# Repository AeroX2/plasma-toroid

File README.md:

# Plasma Toroid

This project is a modification of the amazing project that is currently being hosted here
https://hackaday.io/project/194683-plasma-toroid-sky-guided-pcb-edition

# Notable Changes
- Added USB-PD built in
- Removed the arc lighter, since the parts are hard to find and expensive
  - Will probably revisit this in the future
- Trying out two MOSFETs to see heat dissipation, will update the design once I've determined a winner

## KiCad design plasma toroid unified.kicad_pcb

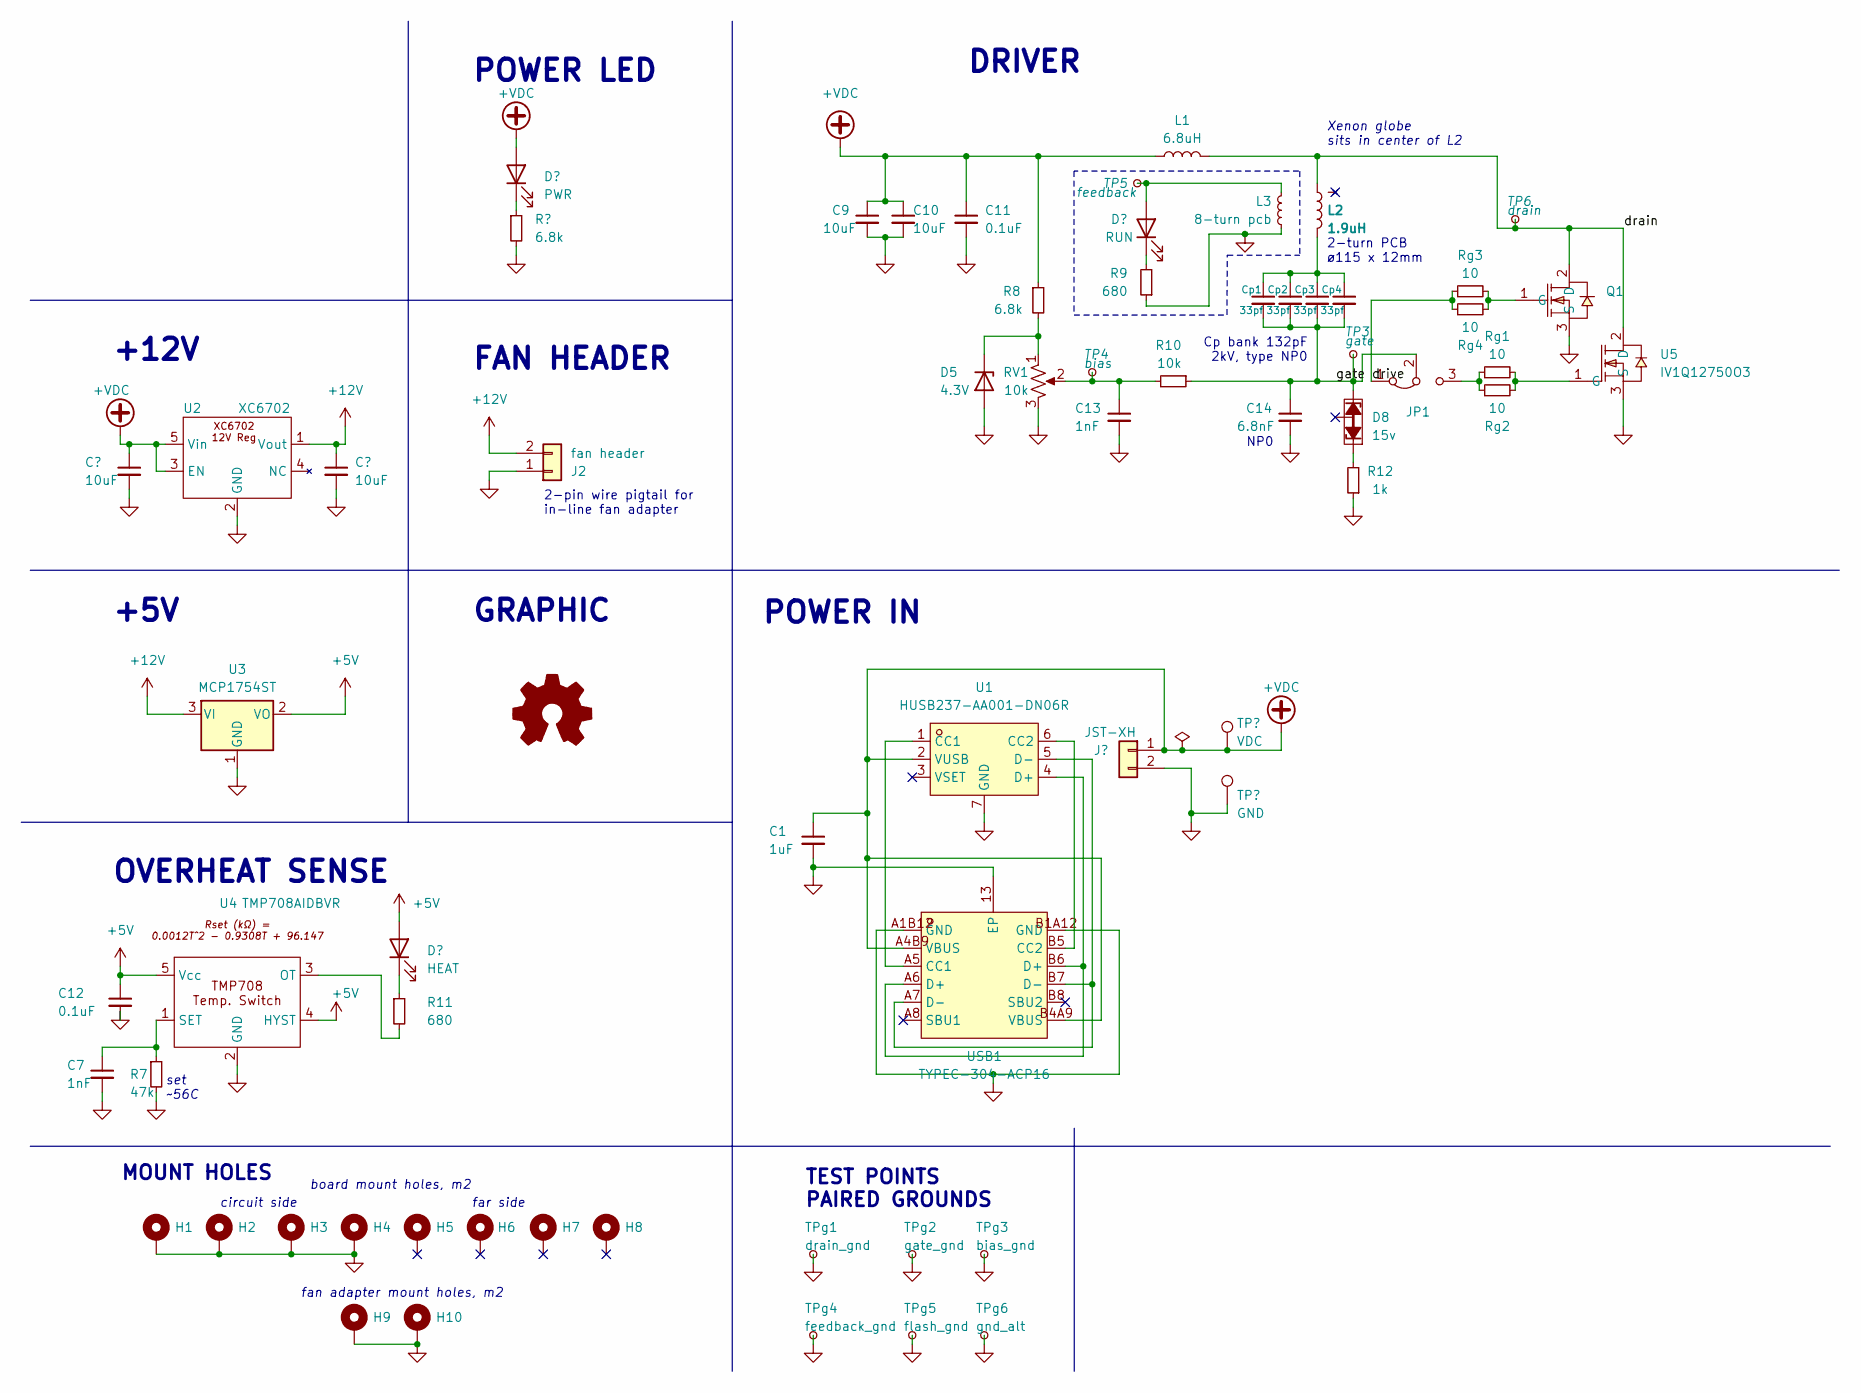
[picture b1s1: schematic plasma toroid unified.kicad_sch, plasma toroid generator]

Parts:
C1: 1uF; C_0603_1608Metric
C4, C5, C9, C10: 10uF; C_1206_3216Metric
C7, C13: 1nF; C_0603_1608Metric
C11, C12: 0.1uF; C_0603_1608Metric
C14: 6.8nF; C_1206_3216Metric
Cp1, Cp2, Cp3, Cp4: 33pf; C_1808_HandSolder
D3: PWR; LED_1206_3216Metric
D5: 4.3V; D_SOD-123
D6: RUN; LED_1206_3216Metric
D7: HEAT; LED_1206_3216Metric
D8: 15v; TSOT-23
H1, H2, H3, H4, H5, H6, H7, H8, H9, H10: MountingHole; MountingHole_2.2mm_M2_Pad_Via_3.75mmHead
J1: JST-XH; JST_PH_B2B-PH-K_1x02_P2.00mm_Vertical
J2: fan header; PinSocket_1x02_P2.00mm_Vertical
JP1: Jumper_3_Bridged12; SolderJumper-3_P1.3mm_Bridged2Bar12_RoundedPad1.0x1.5mm_Num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
L1: 6.8uH; L_Bourns_SRR1260_nosilkscreen
L2: 1.9uH; plasmadonut_inductor_2layer_115mm_integrated
L3: 8-turn pcb; FEEDBACK_COIL
Q1: NCEP02525F; TO-220F-3_L10.2-W4.7-P2.54-L; LCSC Part C503036
R4: 6.8k; R_0603_1608Metric
R7: 47k; R_0603_1608Metric
R8: 6.8k; R_1206_3216Metric
R9, R11: 680; R_0603_1608Metric
R10: 10k; R_1206_3216Metric
R12: 1k; R_1206_3216Metric
RV1: 10k; Potentiometer_Bourns_PTV09A-1_Single_Vertical_larger_mount_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
Rg1, Rg2, Rg3, Rg4: 10; R_2010_5025Metric
SYM1: Logo_Open_Hardware_Small; OSHW-Symbol_6.7x6mm_Copper
TP1: GND; TestPoint_THTPad_D2.0mm_Drill1.0mm
TP2: VDC; TestPoint_THTPad_D2.0mm_Drill1.0mm
TP3: gate; TestPoint_THTPad_D2.0mm_Drill1.0mm
TP4: bias; TestPoint_THTPad_D2.0mm_Drill1.0mm
TP5: feedback; TestPoint_THTPad_D2.0mm_Drill1.0mm
TP6: drain; TestPoint_THTPad_D2.0mm_Drill1.0mm
TPg1: drain_gnd; TestPoint_THTPad_1.0x1.0mm_Drill0.5mm
TPg2: gate_gnd; TestPoint_THTPad_1.0x1.0mm_Drill0.5mm
TPg3: bias_gnd; TestPoint_THTPad_1.0x1.0mm_Drill0.5mm
TPg4: feedback_gnd; TestPoint_THTPad_1.0x1.0mm_Drill0.5mm
TPg5: flash_gnd; TestPoint_THTPad_1.0x1.0mm_Drill0.5mm
TPg6: gnd_alt; TestPoint_THTPad_D2.5mm_Drill1.2mm
U1: HUSB237-AA001-DN06R; TDFN-6_L2.0-W2.0-P0.65-TL-EP; LCSC Part C22373734
U2: XC6702; SOT-89-5
U3: MCP1754ST; SOT-23
U4: TMP708AIDBVR; SOT-23-5
U5: IV1Q12750O3; TO-220-3_L10.2-W4.5-P2.54-L; LCSC Part C2979250
USB1: TYPEC-304-ACP16; USB-C-SMD_TYPE-C-16P-1; LCSC Part C2982555

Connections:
+5V: C12.1, D7.2 (A), U3.2 (VO), U4.4 (HYST), U4.5 (Vcc)
+12V: C5.1, J2.2, U2.1 (Vout), U3.3 (VI)
+VDC: C1.1, C4.1, C9.1, C10.1, C11.1, D3.2 (A), J1.1, L1.1, R8.1, TP2.1, U1.2 (VUSB), U2.3 (EN), U2.5 (Vin), USB1.A4B9 (VBUS), USB1.B4A9 (VBUS)
/drain: L1.2, L2.2, Q1.2 (D), TP6.1, U5.2 (D)
/gate drive: C14.1, Cp1.2, Cp2.2, Cp3.2, Cp4.2, D8.2 (A), JP1.2 (C), R10.1, TP3.1
GND: C1.2, C4.2, C5.2, C7.2, C9.2, C10.2, C11.2, C12.2, C13.2, C14.2, D5.2 (A), H1.1, H2.1, H3.1, H4.1, H9.1, H10.1, J1.2, J2.1, L3.1, Q1.3 (S), R4.2, R7.2, R9.1, R12.1, RV1.3, TP1.1, TPg1.1, TPg2.1, TPg3.1, TPg4.1, TPg5.1, TPg6.1, U1.7 (GND), U2.2 (GND), U3.1 (GND), U4.2 (GND), U5.3 (S), USB1.13 (EP), USB1.A1B12 (GND), USB1.B1A12 (GND)
unnamed: C13.1, R10.2, RV1.2, TP4.1
unnamed: Cp1.1, Cp2.1, Cp3.1, Cp4.1, L2.1
unnamed: D3.1 (K), R4.1
unnamed: D5.1 (K), R8.2, RV1.1
unnamed: D6.2 (A), L3.2, TP5.1
unnamed: D6.1 (K), R9.2
unnamed: D7.1 (K), R11.1
unnamed: D8.1 (K), R12.2
unnamed: JP1.1 (A), Rg3.1, Rg4.1
unnamed: JP1.3 (B), Rg1.1, Rg2.1
unnamed: Q1.1 (G), Rg3.2, Rg4.2
unnamed: U1.1 (CC1), USB1.A5 (CC1)
unnamed: U1.6 (CC2), USB1.B5 (CC2)
unnamed: U1.4 (D+), USB1.A6 (D+), USB1.B6 (D+)
unnamed: U1.5 (D-), USB1.A7 (D-), USB1.B7 (D-)
unnamed: R11.2, U4.3 (OT)
unnamed: C7.1, R7.1, U4.1 (SET)
unnamed: Rg1.2, Rg2.2, U5.1 (G)

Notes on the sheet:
Xenon globe sits in center of L2
POWER IN
TEST POINTS PAIRED GROUNDS
GRAPHIC
board mount holes, m2
DRIVER
FAN HEADER
POWER LED
fan adapter mount holes, m2
NP0
+12V
2-pin wire pigtail for in-line fan adapter
2-turn PCB ø115 x 12mm
MOUNT HOLES
+5V
circuit side
far side
Cp bank 132pF 2kV, type NP0
set ~56C
OVERHEAT SENSE

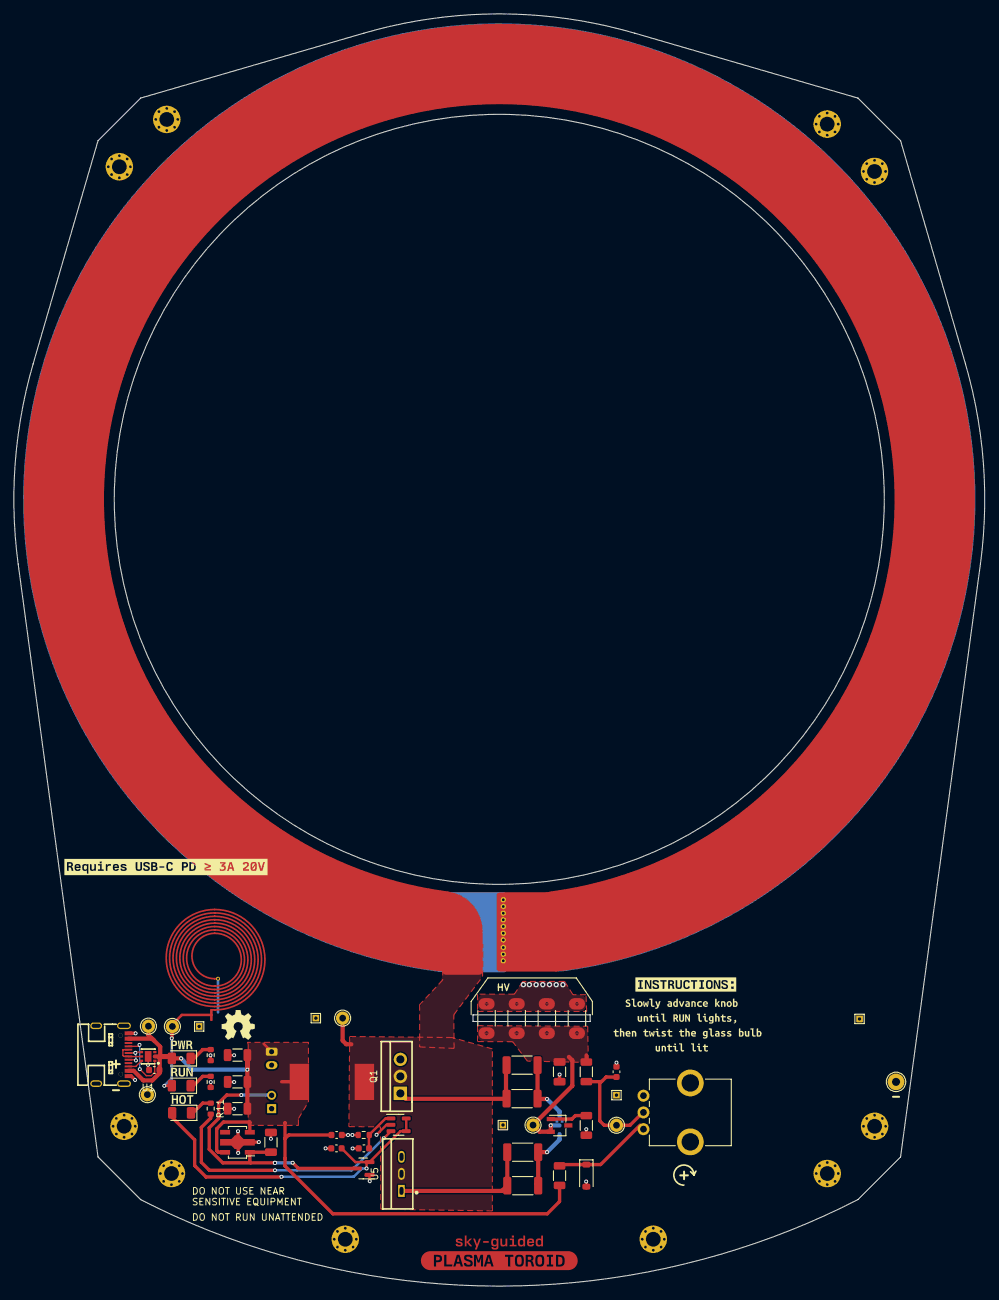
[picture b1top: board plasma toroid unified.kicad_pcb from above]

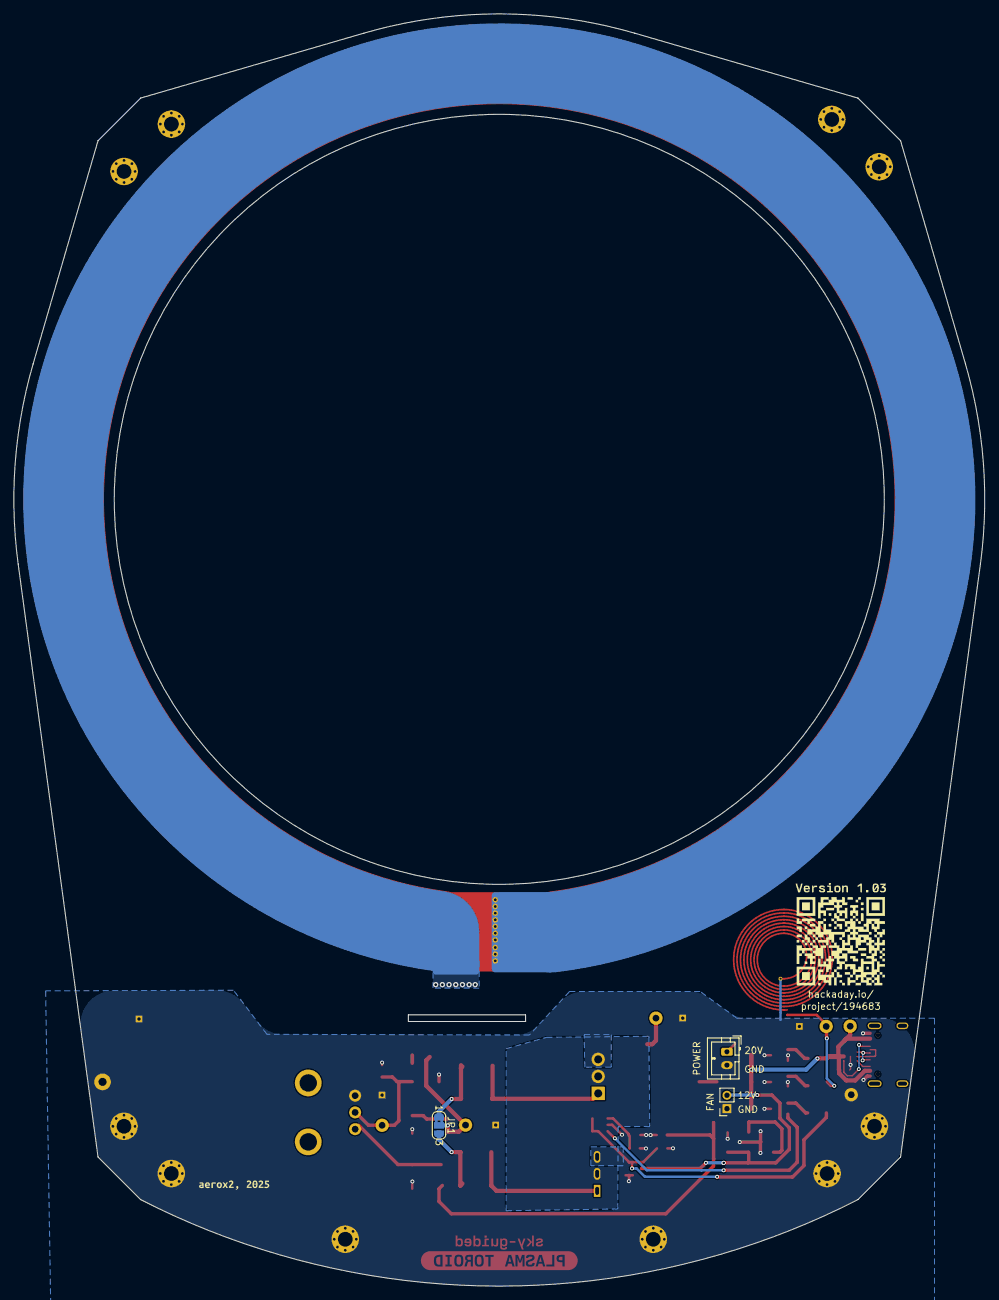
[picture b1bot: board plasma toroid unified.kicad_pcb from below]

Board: 2 copper layers, 145.0 x 190.0 mm, 78 parts (7 on the bottom side), 24 nets.

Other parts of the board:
QR*****: hackaday.io/; hackadayio qr code
kibuzzard-66C555BE: G***; kibuzzard-66C555BE
kibuzzard-66C556E1: G***; kibuzzard-66C556E1
kibuzzard-66C556ED: G***; kibuzzard-66C556ED
kibuzzard-66EB7AC2: G***; kibuzzard-66EB7AC2
kibuzzard-6619ED63: G***; kibuzzard-6619ED63
kibuzzard-6619ED70: G***; kibuzzard-6619ED70
kibuzzard-6619ED77: G***; kibuzzard-6619ED77
kibuzzard-6637F496: G***; kibuzzard-6637F496
kibuzzard-67825B16: G***; kibuzzard-67825B16
kibuzzard-678256E4: G***; kibuzzard-678256E4

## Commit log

2025-01-11 First commit, notable changes, removed arc lighter causes parts were hard to get and expensive, added two different mosfets hopefully one works, USB-C PD built in
